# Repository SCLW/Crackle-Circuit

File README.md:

# Crackle Circuit

> Discrete-transistor recreation of Michel Waisvisz's *Cracklebox*, replacing the obsolete LM709 op-amp with an equivalent built from individual transistors and resistors.

|                       |                                                  |
| :-------------------- | :----------------------------------------------- |
| **Project**           | Crackle Circuit                                  |
| **Status**            | Closed                                           |
| **Started**           | February 2021                                    |
| **Completed**         | March 2021                                       |
| **Duration**          | ~1 month                                         |
| **License (hardware/docs)** | [CC-BY-4.0](cc-by-4.0.md)                  |
| **License (code)**    | [MIT](license-mit.md)                            |

---

## About

In addition to sensors or other control elements like potentiometers, force-sensing resistors, or similar components, touching dedicated connection points in a circuit will also affect its behavior. The human body can add various parameters such as resistance or capacitance. The conductivity of human skin introduced into a circuit varies greatly, just like the capacitance of the human body. Moisture (sweat), pressure, or even the surroundings define the actual electrical values and make it difficult to predict their effect on a circuit. In this context, the *crackle box* should be mentioned as a remarkable example.

*Crackle Box. Photo: Till Kniola*

The crackle box is a touch-controlled electronic instrument, developed in the 1970s by [Michel Waisvisz](https://de.wikipedia.org/wiki/Michel_Waisvisz) (\*1949 Leiden † 2008 Amsterdam) at [STEIM](https://de.wikipedia.org/wiki/Steim "Studio voor ElektroInstrumental Muziek") in Amsterdam. Its beginnings date back to the 1960s. It is a small, battery-operated wooden case (14 × 8 × 3 cm), like a cigar box, with a visible circuit board featuring six distinctive touch points (~1 cm² each) and an on/off switch. Underneath the touch surface is a built-in loudspeaker. The vibrating air can pass through a number of holes in the PCB between the touch surfaces. The instrument produces random noise, clicks and plops, or oscillates when touched with fingers. The circuit inside is just an op-amp in an inverting configuration, while many circuit points and most pins of the op-amp are made available on the outside of the device as conductive touch pads.

*LM709 TO-5 metal can packages*

The device makes use of the LM709/μA709 op-amp (originally National Semiconductor, then Texas Instruments), one of the earliest monolithic operational amplifiers, created by [Robert Widlar](https://en.wikipedia.org/wiki/Bob_Widlar). Its design concept and performance were soon surpassed by its successor, the LM741. While the latter is still in production, the LM709 has been discontinued. Compared with modern op-amps, the LM709 lacks an output buffer stage, which means it is not short-circuit proof. Furthermore, it does not have internal frequency compensation: external components must be added to limit the op-amp's bandwidth and prevent unwanted oscillation. Richard Kaußler has produced a detailed analysis of the LM709, which can be found [here](https://www.richis-lab.de/Opamp20.htm "LM709"). His [website](https://www.richis-lab.de/ "Richi's Lab") (in German) is a good resource for in-depth information about the internal structure of various ICs.

*Die of an LM709 op-amp. Photo: Richard Kaußler*

The image above shows the [die](https://en.wikipedia.org/wiki/Die_(integrated_circuit)) of the LM709 embedded in a TO-5 package, alongside a close-up. The die is the integrated circuit made of silicon. The design of the crackle box focuses on the imperfections of the LM709 and its special features, particularly its external frequency compensation. Michel Waisvisz's crackle box is therefore an early example of circuit bending and the unconventional use of electronic components. The crackle box was reissued over the following decades as assembly kits, and could still be ordered directly from STEIM. STEIM itself ceased to exist as an organisation at the end of 2020, after the Dutch arts council ended its structural funding. See [assets/documents/sources.md](assets/documents/sources.md) for further reading.

*LM709 pinout and schematic of Michel Waisvisz's crackle box*

## Approach: substituting the LM709 with discrete components

As mentioned above, the LM709 is out of production and most modern op-amps are internally frequency-compensated and achieve high stability during operation. For the crackle box, the LM709 cannot simply be substituted with another op-amp without losing the instrument's character. This is part of the broader problem of obsolescence in the field of historical electronic instruments. One approach to circumvent it is to look more closely at the LM709 itself: the internal schematic can be found in its datasheet.

*Schematic with LM709 equivalent internal circuit*

For most applications, building an integrated circuit from discrete parts leads to a significant degradation in performance. This is because the components within an IC are fabricated to precisely meet the needs of the circuit.

*Breadboard with discrete components substituting the LM709*

Since the crackle box doesn't rely on precise operation but rather on randomness, standard transistors can be used. Both schematics presented here omit the push-pull speaker driver, which is built from two complementary pairs of transistors. Substituting the obsolete LM709 with discrete components, specifically transistors and resistors, brings an equivalent crackle circuit into being.

*Crackle board*

## Repository contents

| Folder                | Contents                                                                          |
| :-------------------- | :-------------------------------------------------------------------------------- |
| `assets/`             | All project content (see subfolders below)                                        |
| `assets/eagle/`       | EAGLE schematic and board source files (Autodesk EAGLE 9 / Fusion Electronics)    |
| `assets/schematic/`   | PDF/SVG exports of the schematic for offline viewing                              |
| `assets/gerber/`      | Gerber and drill files for PCB fabrication                                        |
| `assets/bom/`         | Bill of materials with Mouser and manufacturer part numbers                       |
| `assets/documents/`   | External references (linked, not bundled). See [sources.md](assets/documents/sources.md) |
| `assets/img/`         | Project photos and figures used in this README                                    |

## Status

The board in this repository is the prototype as fabricated in March 2021 and has not been fully re-verified since. A transistor may be in the wrong orientation somewhere in the design (schematic symbol, footprint, or board file). Please do not order multiple PCBs from this design yet. I will check the board soon and post any errata here, although the repository is otherwise closed.

The design is a small (~50 × 55 mm) two-layer through-hole PCB populated from the [Bill of Materials](assets/bom/readme.md): metal-film resistors, film capacitors, 13× 2N3904 (NPN) and 2× 2N3906 (PNP) in TO-92, and a 2×7 pin header. Power follows the original LM709 setup, a small bipolar (±9 V) or single-supply battery arrangement; the circuit is forgiving.

## License

The hardware design files (schematic, board, Gerbers) and this documentation are released under [Creative Commons Attribution 4.0 International (CC-BY-4.0)](cc-by-4.0.md). Any code or firmware in this repository (none at present, included for future contributions) is released under [the MIT License](license-mit.md).

When using or adapting the design, please credit:

> *Lorenz Schwarz, Crackle Circuit (2021). https://github.com/SCLW/Crackle-Circuit*

A [`CITATION.cff`](CITATION.cff) file is provided so GitHub will surface a *"Cite this repository"* button automatically.

## Credits

- **Original concept:** Michel Waisvisz, STEIM (Amsterdam, 1969–2020)
- **LM709 op-amp:** Robert Widlar, National Semiconductor (1965)
- **Photo *Crackle Box*:** Till Kniola
- **Photo *LM709 die*:** Richard Kaußler, [Richi's Lab](https://www.richis-lab.de/)
- **Discrete substitution and PCB design:** Lorenz Schwarz (2021)

## Related work

The Crackle Circuit belongs to a broader family of touch-controlled DIY noise instruments. The most direct kindred spirit is John Richards's *Dirty Electronics* project (Leicester, since 2003), which has produced a long line of cracklebox-style touch instruments around different cheap ICs, notably a build around a CMOS hex inverter (the 4049, used as a chaotic oscillator in the Forrest-Mims tradition) and another around the LM358 dual op-amp. Both are excellent points of comparison for the Crackle Circuit and worth seeking out for anyone interested in the lineage. See <https://www.dirtyelectronics.org/>.

## Further reading

See [`assets/documents/sources.md`](assets/documents/sources.md) for links to the LM709 datasheet, Robert Widlar's *Application Note 4*, Richard Kaußler's analysis of the LM709 die, John Richards's Dirty Electronics, and Andi Otto's *The STEIM Touch* (Goldsmiths Press), the academic history of STEIM's instrument-building decades.

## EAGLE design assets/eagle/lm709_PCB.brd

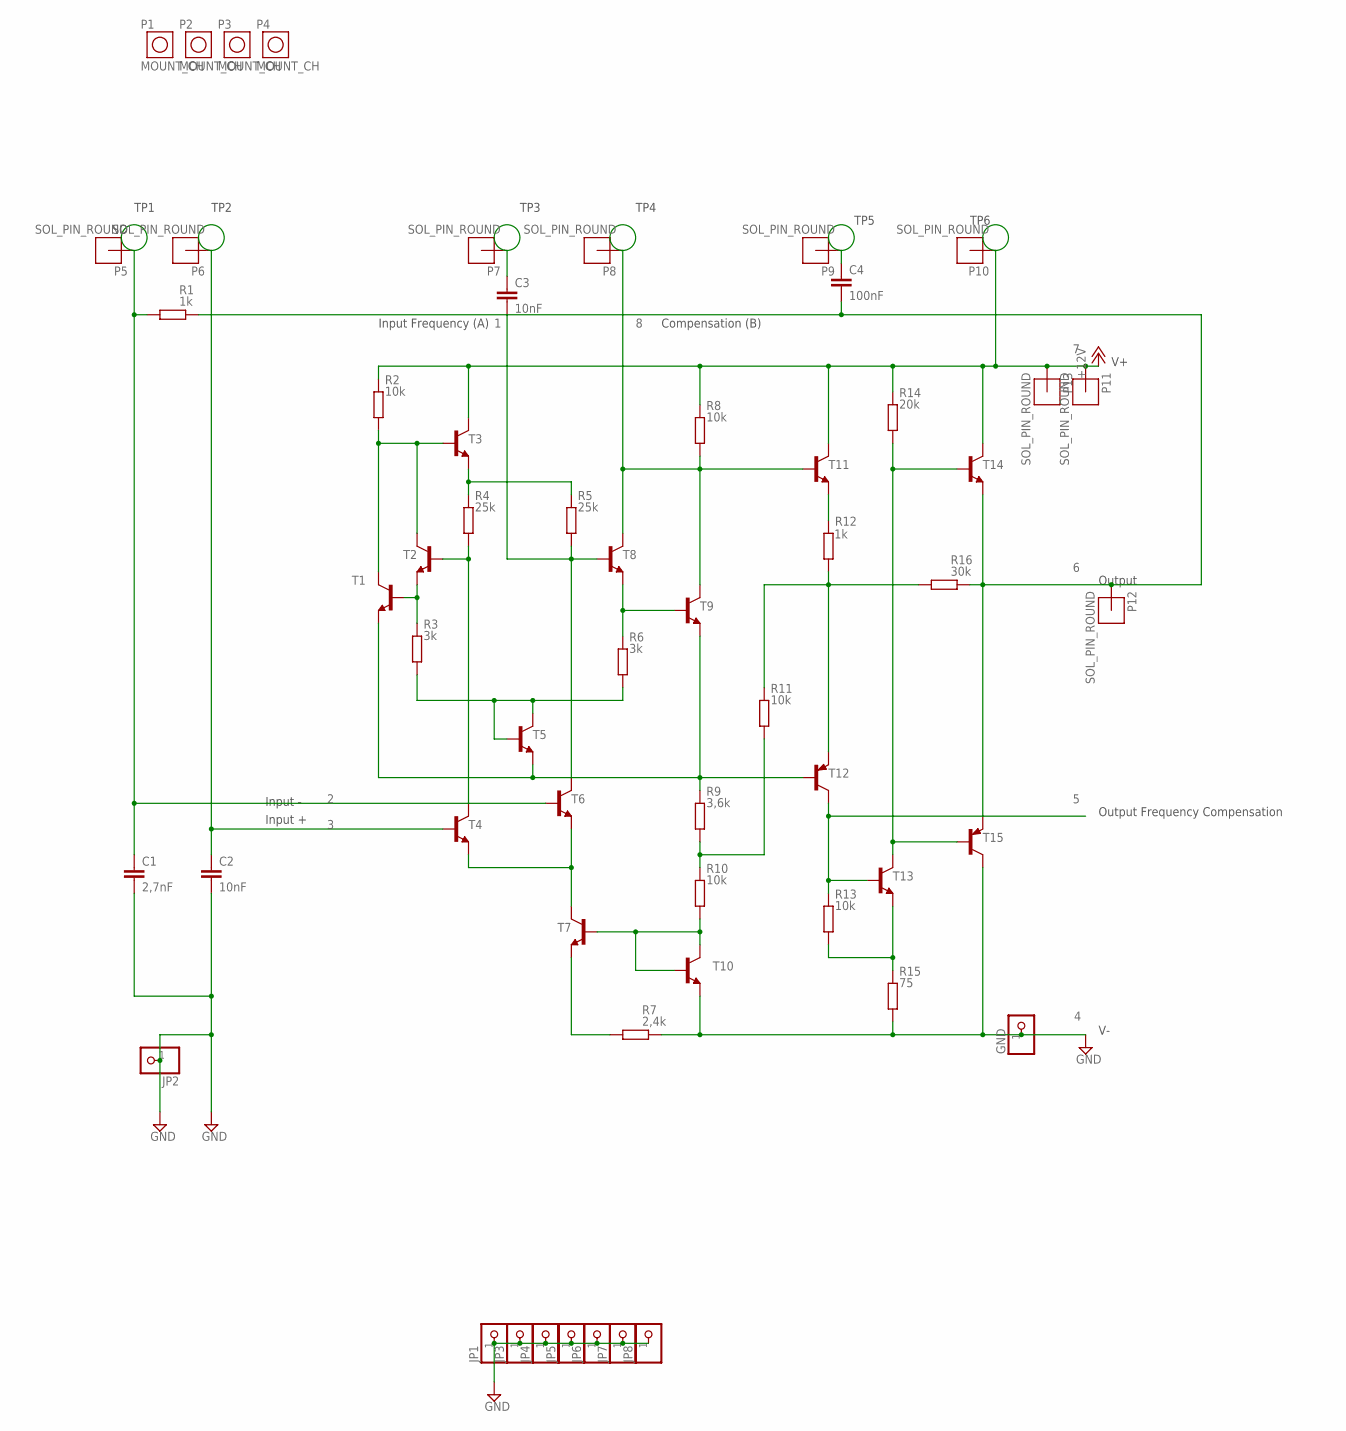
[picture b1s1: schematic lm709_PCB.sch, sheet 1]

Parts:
C1: 2,7nF; C050-024X044
C2, C3: 10nF; C050-024X044
C4: 100nF; C050-024X044
GND: PINHD-1X1; 1X01
JP1, JP2, JP3, JP4, JP5, JP6, JP7, JP8: PINHD-1X1; 1X01
P1, P2, P3, P4: MOUNT_CH; MOUNT_CH32
P5, P6, P7, P8, P9, P10, P11, P12, P13: SOL_PIN_ROUND; SOL_PAD_ROUND
R1, R12: 1k; 0207/10
R2, R8, R10, R11, R13: 10k; 0207/10
R3, R6: 3k; 0207/10
R4, R5: 25k; 0207/10
R7: 2,4k; 0207/10
R9: 3,6k; 0207/10
R14: 20k; 0207/10
R15: 75; 0207/10
R16: 30k; 0207/10
T1, T2, T3, T4, T5, T6, T7, T8, T9, T10, T11, T13, T14: 2N3904-NPN-TO92-EBC; TO92-EBC
T12, T15: 2N3906-PNP-TO92-EBC; TO92-EBC

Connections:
+12V: P10.1, P11.1, P13.1, R2.2, R8.2, R14.2, T3.C, T11.C, T14.C
GND: C1.2, C2.2, GND.1, JP1.1, JP2.1, JP3.1, JP4.1, JP5.1, JP6.1, JP7.1, JP8.1, R7.1, R15.2, T10.E, T15.C
unnamed: R3.2, T1.B, T2.E
unnamed: R4.1, T2.B, T4.C
unnamed: R4.2, R5.2, T3.E
unnamed: R2.1, T1.C, T2.C, T3.B
unnamed: R6.2, T8.E, T9.B
unnamed: C3.2, R5.1, T6.C, T8.B
unnamed: R3.1, R6.1, T5.B, T5.C
unnamed: R9.2, T1.E, T5.E, T9.E, T12.B
unnamed: R14.1, T13.C, T14.B, T15.B
unnamed: C2.1, P6.1, T4.B
unnamed: C1.1, P5.1, R1.2, T6.B
unnamed: T4.E, T6.E, T7.C
unnamed: R7.2, T7.E
unnamed: R10.1, T7.B, T10.B, T10.C
unnamed: R9.1, R10.2, R11.1
unnamed: P8.1, R8.1, T8.C, T9.C, T11.B
unnamed: R13.1, T12.C, T13.B
unnamed: C4.2, P12.1, R1.1, R16.1, T14.E, T15.E
unnamed: R11.2, R12.1, R16.2, T12.E
unnamed: R12.2, T11.E
unnamed: R13.2, R15.1, T13.E
unnamed: C3.1, P7.1
unnamed: C4.1, P9.1

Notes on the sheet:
Input Frequency (A)
Compensation (B)
Input -
Input +
Output
Output Frequency Compensation
TP1
TP2
TP3
TP4
TP5
TP6

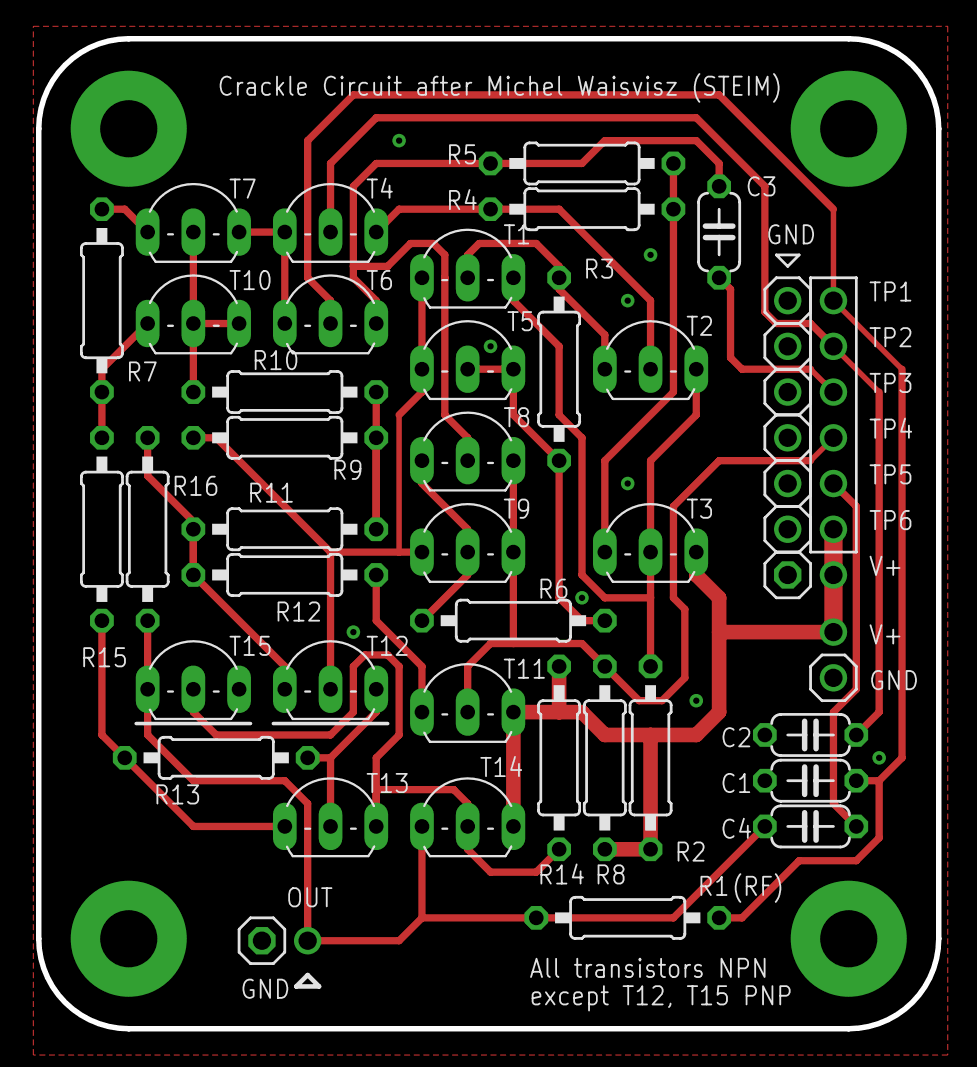
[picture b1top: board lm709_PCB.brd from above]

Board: 2 copper layers, 50.0 x 55.0 mm, 57 parts (0 on the bottom side), 25 nets.

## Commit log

2026-05-07 Update repository

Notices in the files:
README.md:
License: CC BY 4.0
Code License: MIT
